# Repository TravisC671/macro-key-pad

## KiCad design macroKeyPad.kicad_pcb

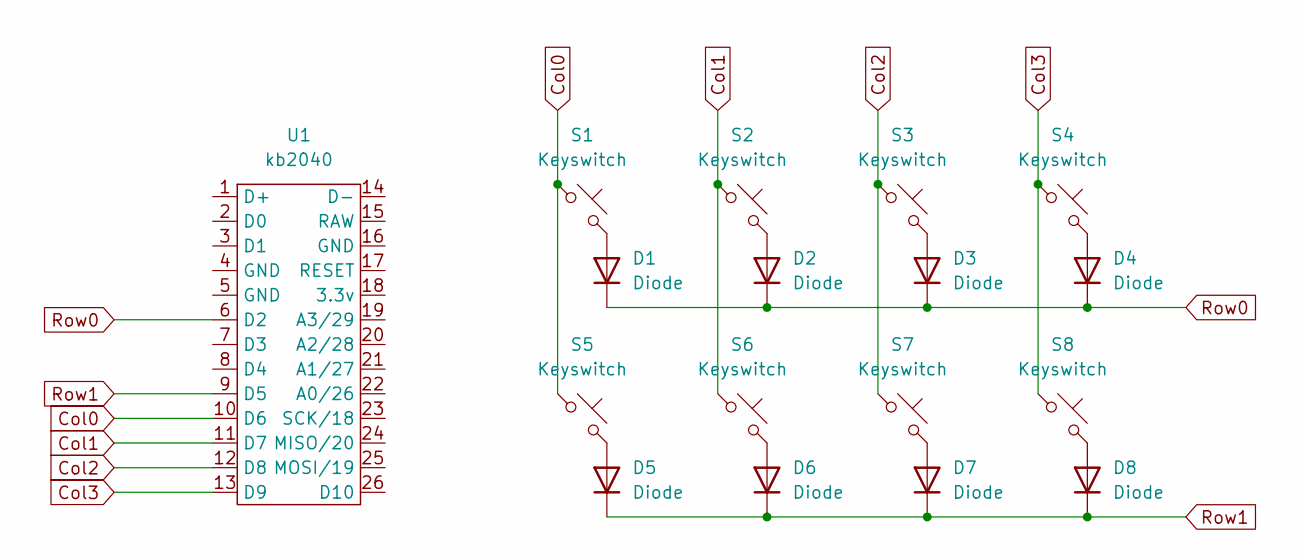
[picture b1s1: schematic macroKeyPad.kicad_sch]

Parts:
D1, D2, D3, D4, D5, D6, D7, D8: Diode; Diode_SOD-123
S1, S2, S3, S4, S5, S6, S7, S8: Keyswitch; SW_Kailh_Choc_V1
U1: kb2040; Adafruit_KB2040_SMD

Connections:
Col0: S1.1, S5.1, U1.10 (D6)
Col1: S2.1, S6.1, U1.11 (D7)
Col2: S3.1, S7.1, U1.12 (D8)
Col3: S4.1, S8.1, U1.13 (D9)
unnamed: D1.2 (A), S1.2
unnamed: D2.2 (A), S2.2
unnamed: D3.2 (A), S3.2
unnamed: D4.2 (A), S4.2
unnamed: D5.2 (A), S5.2
unnamed: D6.2 (A), S6.2
unnamed: D7.2 (A), S7.2
unnamed: D8.2 (A), S8.2
Row0: D1.1 (K), D2.1 (K), D3.1 (K), D4.1 (K), U1.6 (D2)
Row1: D5.1 (K), D6.1 (K), D7.1 (K), D8.1 (K), U1.9 (D5)

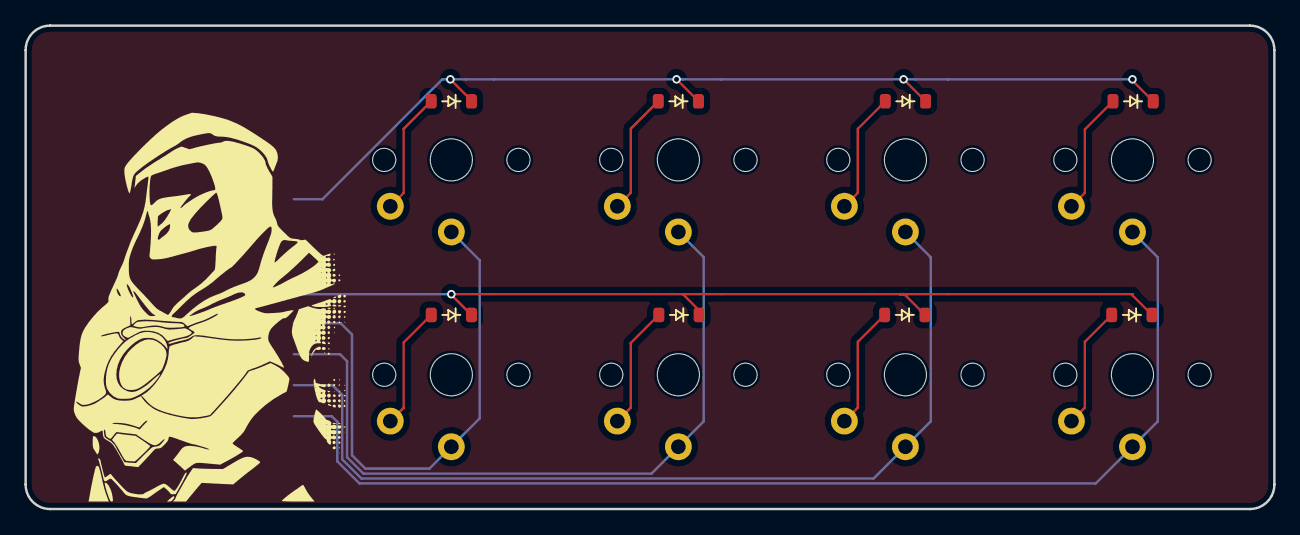
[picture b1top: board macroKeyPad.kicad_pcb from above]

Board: 2 copper layers, 102.3 x 39.6 mm, 17 parts (1 on the bottom side), 14 nets.

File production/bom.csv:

Designator,Footprint,Quantity,Value,LCSC Part #
"D1, D2, D3, D4, D5, D6, D7, D8",Diode_SOD-123,8,Diode,
"S1, S2, S3, S4, S5, S6, S7, S8",SW_Kailh_Choc_V1,8,Keyswitch,
U1,Adafruit_KB2040_SMD,1,kb2040,

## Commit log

2025-05-29 added libraries and changed structure
2025-05-30 added libraries
    Almost done, gotta add graphic and possibly change the thing for the kb2040
2025-05-31 pretty close to being done
2025-05-31 wiring
2025-05-31 added image and routes
2025-05-31 almost ready for production
2025-06-03 quick fix
2025-06-03 quick change again
2025-06-29 Updated Via Size and switch footprint
2025-06-30 finalizing art and creating housing
2025-07-09 added final touches
    gonna have it checked and then purchase the board
2025-07-10 ordered!
